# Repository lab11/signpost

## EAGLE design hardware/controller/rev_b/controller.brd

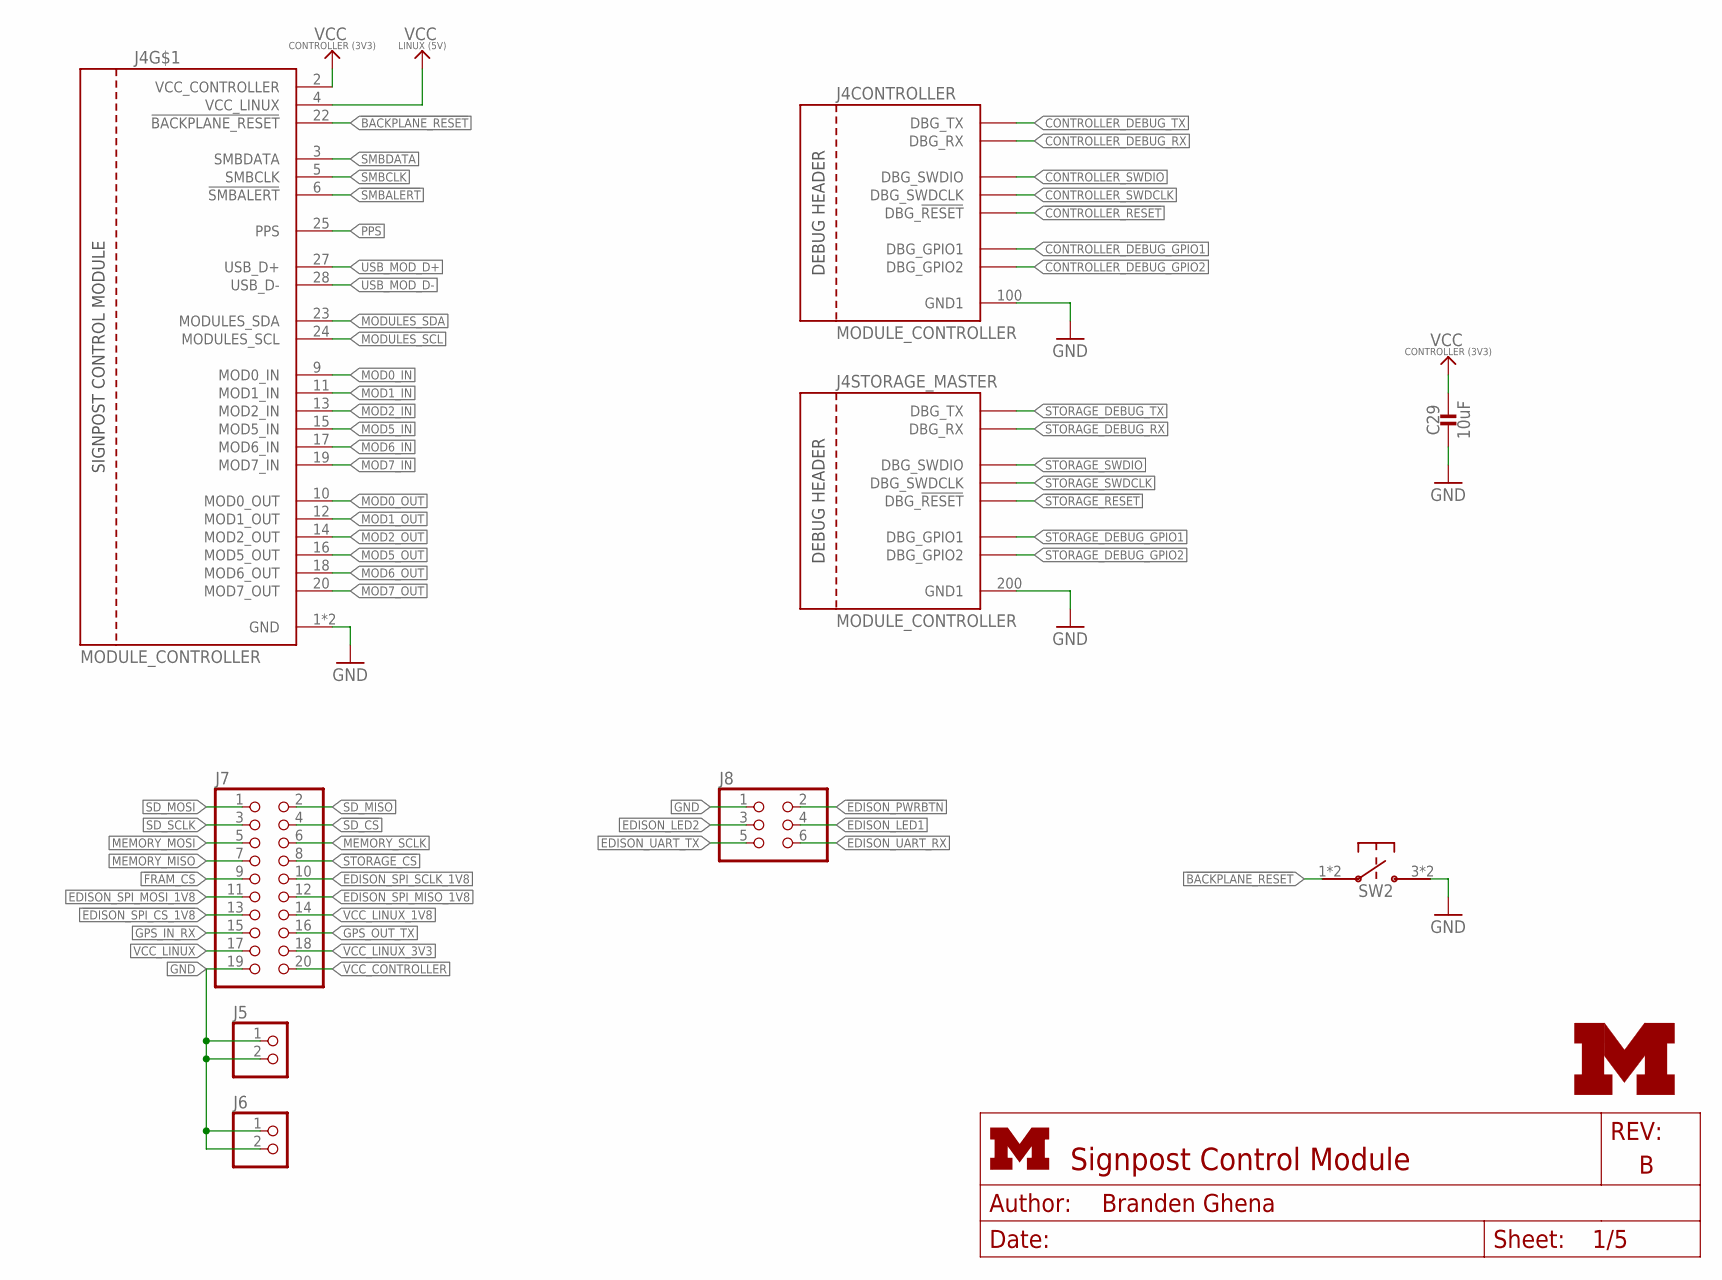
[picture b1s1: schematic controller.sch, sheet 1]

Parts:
C29: 10uF; 0402_CAP; DIGIKEY 490-13811-1-ND
J4: MODULE_CONTROLLER
J5, J6: PINHD-1X2; 1X02
J7: PINHD-2X10; 2X10
J8: PINHD-2X3; 2X03
LOGO1: UMICH_SOLID_MEDIUM; UMICH_SOLID_200MIL
SW2: PTS810SJ

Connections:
!BACKPLANE_RESET: J4.22 (!BACKPLANE_RESET), SW2.1, SW2.2
!CONTROLLER_RESET: J4.105 (DBG_!RESET); also elsewhere on the board
!EDISON_PWRBTN: J8.2; also elsewhere on the board
!EDISON_SPI_CS_1V8: J7.13; also elsewhere on the board
!FRAM_CS: J7.9; also elsewhere on the board
!SD_CS: J7.4; also elsewhere on the board
!SMBALERT: J4.6 (!SMBALERT); also elsewhere on the board
!STORAGE_CS: J7.8; also elsewhere on the board
!STORAGE_RESET: J4.205 (DBG_!RESET); also elsewhere on the board
CONTROLLER_DEBUG_GPIO1: J4.101 (DBG_GPIO1); also elsewhere on the board
CONTROLLER_DEBUG_GPIO2: J4.104 (DBG_GPIO2); also elsewhere on the board
CONTROLLER_DEBUG_RX: J4.103 (DBG_RX); also elsewhere on the board
CONTROLLER_DEBUG_TX: J4.102 (DBG_TX); also elsewhere on the board
CONTROLLER_SWDCLK: J4.106 (DBG_SWDCLK); also elsewhere on the board
CONTROLLER_SWDIO: J4.107 (DBG_SWDIO); also elsewhere on the board
EDISON_LED1: J8.4; also elsewhere on the board
EDISON_LED2: J8.3; also elsewhere on the board
EDISON_SPI_MISO_1V8: J7.12; also elsewhere on the board
EDISON_SPI_MOSI_1V8: J7.11; also elsewhere on the board
EDISON_SPI_SCLK_1V8: J7.10; also elsewhere on the board
EDISON_UART_RX: J8.6; also elsewhere on the board
EDISON_UART_TX: J8.5; also elsewhere on the board
GND: C29.2, J4.1 (GND), J4.21 (GND), J4.100 (GND1), J4.200 (GND1), J5.1, J5.2, J6.1, J6.2, J7.19, J8.1, SW2.3, SW2.4; also elsewhere on the board
GPS_IN_RX: J7.15; also elsewhere on the board
GPS_OUT_TX: J7.16; also elsewhere on the board
MEMORY_MISO: J7.7; also elsewhere on the board
MEMORY_MOSI: J7.5; also elsewhere on the board
MEMORY_SCLK: J7.6; also elsewhere on the board
MOD0_IN: J4.9 (MOD0_IN); also elsewhere on the board
MOD0_OUT: J4.10 (MOD0_OUT); also elsewhere on the board
MOD1_IN: J4.11 (MOD1_IN); also elsewhere on the board
MOD1_OUT: J4.12 (MOD1_OUT); also elsewhere on the board
MOD2_IN: J4.13 (MOD2_IN); also elsewhere on the board
MOD2_OUT: J4.14 (MOD2_OUT); also elsewhere on the board
MOD5_IN: J4.15 (MOD5_IN); also elsewhere on the board
MOD5_OUT: J4.16 (MOD5_OUT); also elsewhere on the board
MOD6_IN: J4.17 (MOD6_IN); also elsewhere on the board
MOD6_OUT: J4.18 (MOD6_OUT); also elsewhere on the board
MOD7_IN: J4.19 (MOD7_IN); also elsewhere on the board
MOD7_OUT: J4.20 (MOD7_OUT); also elsewhere on the board
MODULES_SCL: J4.24 (MODULES_SCL); also elsewhere on the board
MODULES_SDA: J4.23 (MODULES_SDA); also elsewhere on the board
PPS: J4.25 (PPS); also elsewhere on the board
SD_MISO: J7.2; also elsewhere on the board
SD_MOSI: J7.1; also elsewhere on the board
SD_SCLK: J7.3; also elsewhere on the board
SMBCLK: J4.5 (SMBCLK); also elsewhere on the board
SMBDATA: J4.3 (SMBDATA); also elsewhere on the board
STORAGE_DEBUG_GPIO1: J4.201 (DBG_GPIO1); also elsewhere on the board
STORAGE_DEBUG_GPIO2: J4.204 (DBG_GPIO2); also elsewhere on the board
STORAGE_DEBUG_RX: J4.203 (DBG_RX); also elsewhere on the board
STORAGE_DEBUG_TX: J4.202 (DBG_TX); also elsewhere on the board
STORAGE_SWDCLK: J4.206 (DBG_SWDCLK); also elsewhere on the board
STORAGE_SWDIO: J4.207 (DBG_SWDIO); also elsewhere on the board
USB_MOD_D+: J4.27 (USB_D+); also elsewhere on the board
USB_MOD_D-: J4.28 (USB_D-); also elsewhere on the board
VCC_CONTROLLER: C29.1, J4.2 (VCC_CONTROLLER), J7.20; also elsewhere on the board
VCC_LINUX: J4.4 (VCC_LINUX), J7.17; also elsewhere on the board
VCC_LINUX_1V8: J7.14; also elsewhere on the board
VCC_LINUX_3V3: J7.18; also elsewhere on the board

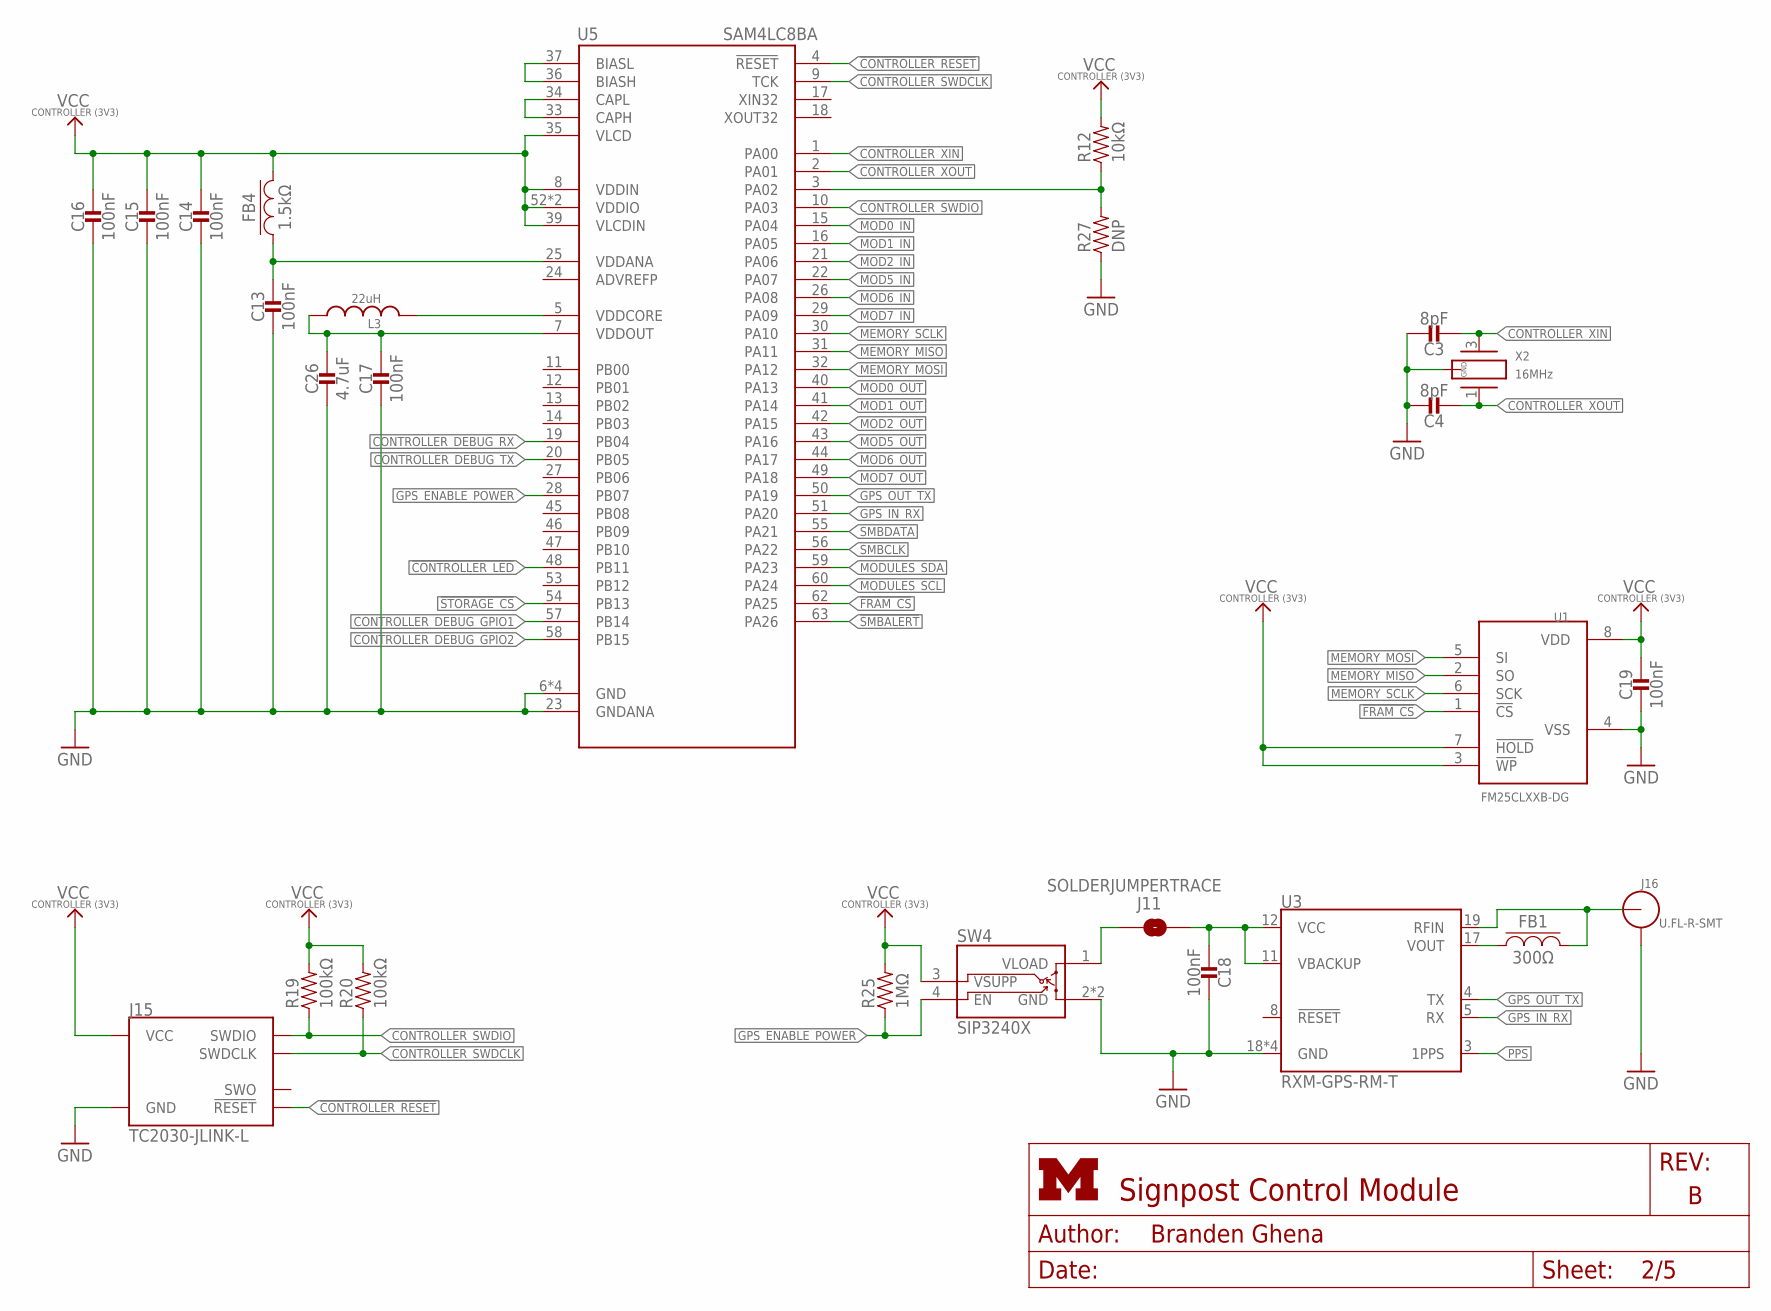
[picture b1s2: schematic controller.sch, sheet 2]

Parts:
C3, C4: 8pF; 0402_CAP; DIGIKEY 490-8230-1-ND
C13, C14, C15, C16, C17, C18, C19: 100nF; 0402_CAP; DIGIKEY 490-10777-1-ND
C26: 4.7uF; 0402_CAP; DIGIKEY 490-13252-1-ND
FB1: 300Ω; 0402_CAP; DIGIKEY ACML-0402-301-TCT-ND
FB4: 1.5kΩ; 0402_CAP; DIGIKEY 1276-6395-1-ND
J11: SOLDERJUMPERTRACE; SJ_2S-TRACE
J15: TC2030-JLINK-L; TC2030-IDC
J16: U.FL-R-SMT; U.FL_SMT
L3: 22uH; 1212
R12: 10kΩ; 0402_RES; DIGIKEY 1276-3431-1-ND
R19, R20: 100kΩ; 0402_RES; DIGIKEY 1276-3432-1-ND
R25: 1MΩ; 0402_RES; DIGIKEY 1276-3433-1-ND
R27: DNP; 0402_RES; DIGIKEY 1276-3431-1-ND
SW4: SIP3240X; TDFN4
U1: FM25CLXXB-DG; TDFN-8; DIGIKEY FM25CL64B-DGRA-ND
U3: RXM-GPS-RM-T
U5: SAM4LC8BA; QFN-64-9MM
X2: 16MHz; FHXXX

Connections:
!CONTROLLER_LED: U5.48 (PB11); also elsewhere on the board
!CONTROLLER_RESET: J15.3 (!RESET), U5.4 (!RESET); also elsewhere on the board
!FRAM_CS: U1.1 (!CS), U5.62 (PA25); also elsewhere on the board
!SMBALERT: U5.63 (PA26); also elsewhere on the board
!STORAGE_CS: U5.54 (PB13); also elsewhere on the board
CONTROLLER_BUCK/LDO_N: R12.1, R27.2, U5.3 (PA02)
CONTROLLER_DEBUG_GPIO1: U5.57 (PB14); also elsewhere on the board
CONTROLLER_DEBUG_GPIO2: U5.58 (PB15); also elsewhere on the board
CONTROLLER_DEBUG_RX: U5.19 (PB04); also elsewhere on the board
CONTROLLER_DEBUG_TX: U5.20 (PB05); also elsewhere on the board
CONTROLLER_SWDCLK: J15.4 (SWDCLK), R20.1, U5.9 (TCK); also elsewhere on the board
CONTROLLER_SWDIO: J15.2 (SWDIO), R19.1, U5.10 (PA03); also elsewhere on the board
CONTROLLER_XIN: C3.1, U5.1 (PA00), X2.3 (2)
CONTROLLER_XOUT: C4.1, U5.2 (PA01), X2.1
GND: C3.2, C4.2, C13.2, C14.2, C15.2, C16.2, C17.2, C18.2, C19.2, C26.2, J15.5 (GND), J16.GND1, J16.GND2, R27.1, SW4.2 (GND), SW4.PAD (GND), U1.4 (VSS), U3.18 (GND), U3.20 (GND), U3.21 (GND), U3.22 (GND), U5.6 (GND), U5.23 (GNDANA), U5.38 (GND), U5.64 (GND), U5.GND, X2.2 (GND), X2.4 (GND); also elsewhere on the board
GPS_ENABLE_POWER: R25.1, SW4.4 (EN), U5.28 (PB07)
GPS_IN_RX: U3.5 (RX), U5.51 (PA20); also elsewhere on the board
GPS_OUT_TX: U3.4 (TX), U5.50 (PA19); also elsewhere on the board
MEMORY_MISO: U1.2 (SO), U5.31 (PA11); also elsewhere on the board
MEMORY_MOSI: U1.5 (SI), U5.32 (PA12); also elsewhere on the board
MEMORY_SCLK: U1.6 (SCK), U5.30 (PA10); also elsewhere on the board
MOD0_IN: U5.15 (PA04); also elsewhere on the board
MOD0_OUT: U5.40 (PA13); also elsewhere on the board
MOD1_IN: U5.16 (PA05); also elsewhere on the board
MOD1_OUT: U5.41 (PA14); also elsewhere on the board
MOD2_IN: U5.21 (PA06); also elsewhere on the board
MOD2_OUT: U5.42 (PA15); also elsewhere on the board
MOD5_IN: U5.22 (PA07); also elsewhere on the board
MOD5_OUT: U5.43 (PA16); also elsewhere on the board
MOD6_IN: U5.26 (PA08); also elsewhere on the board
MOD6_OUT: U5.44 (PA17); also elsewhere on the board
MOD7_IN: U5.29 (PA09); also elsewhere on the board
MOD7_OUT: U5.49 (PA18); also elsewhere on the board
MODULES_SCL: U5.60 (PA24); also elsewhere on the board
MODULES_SDA: U5.59 (PA23); also elsewhere on the board
unnamed: FB1.1, U3.17 (VOUT)
unnamed: FB1.2, J16.SIG (ANT), U3.19 (RFIN)
unnamed: J11.1, SW4.1 (VLOAD)
unnamed: C13.1, FB4.1, U5.25 (VDDANA)
unnamed: C17.1, C26.1, L3.P$1 (1), U5.7 (VDDOUT)
unnamed: U5.36 (BIASH), U5.37 (BIASL)
unnamed: U5.33 (CAPH), U5.34 (CAPL)
unnamed: C18.1, J11.2, U3.11 (VBACKUP), U3.12 (VCC)
unnamed: L3.P$2 (2), U5.5 (VDDCORE)
PPS: U3.3 (1PPS); also elsewhere on the board
SMBCLK: U5.56 (PA22); also elsewhere on the board
SMBDATA: U5.55 (PA21); also elsewhere on the board
VCC_CONTROLLER: C14.1, C15.1, C16.1, C19.1, FB4.2, J15.1 (VCC), R12.2, R19.2, R20.2, R25.2, SW4.3 (VSUPP), U1.3 (!WP), U1.7 (!HOLD), U1.8 (VDD), U5.8 (VDDIN), U5.35 (VLCD), U5.39 (VLCDIN), U5.52 (VDDIO), U5.61 (VDDIO); also elsewhere on the board

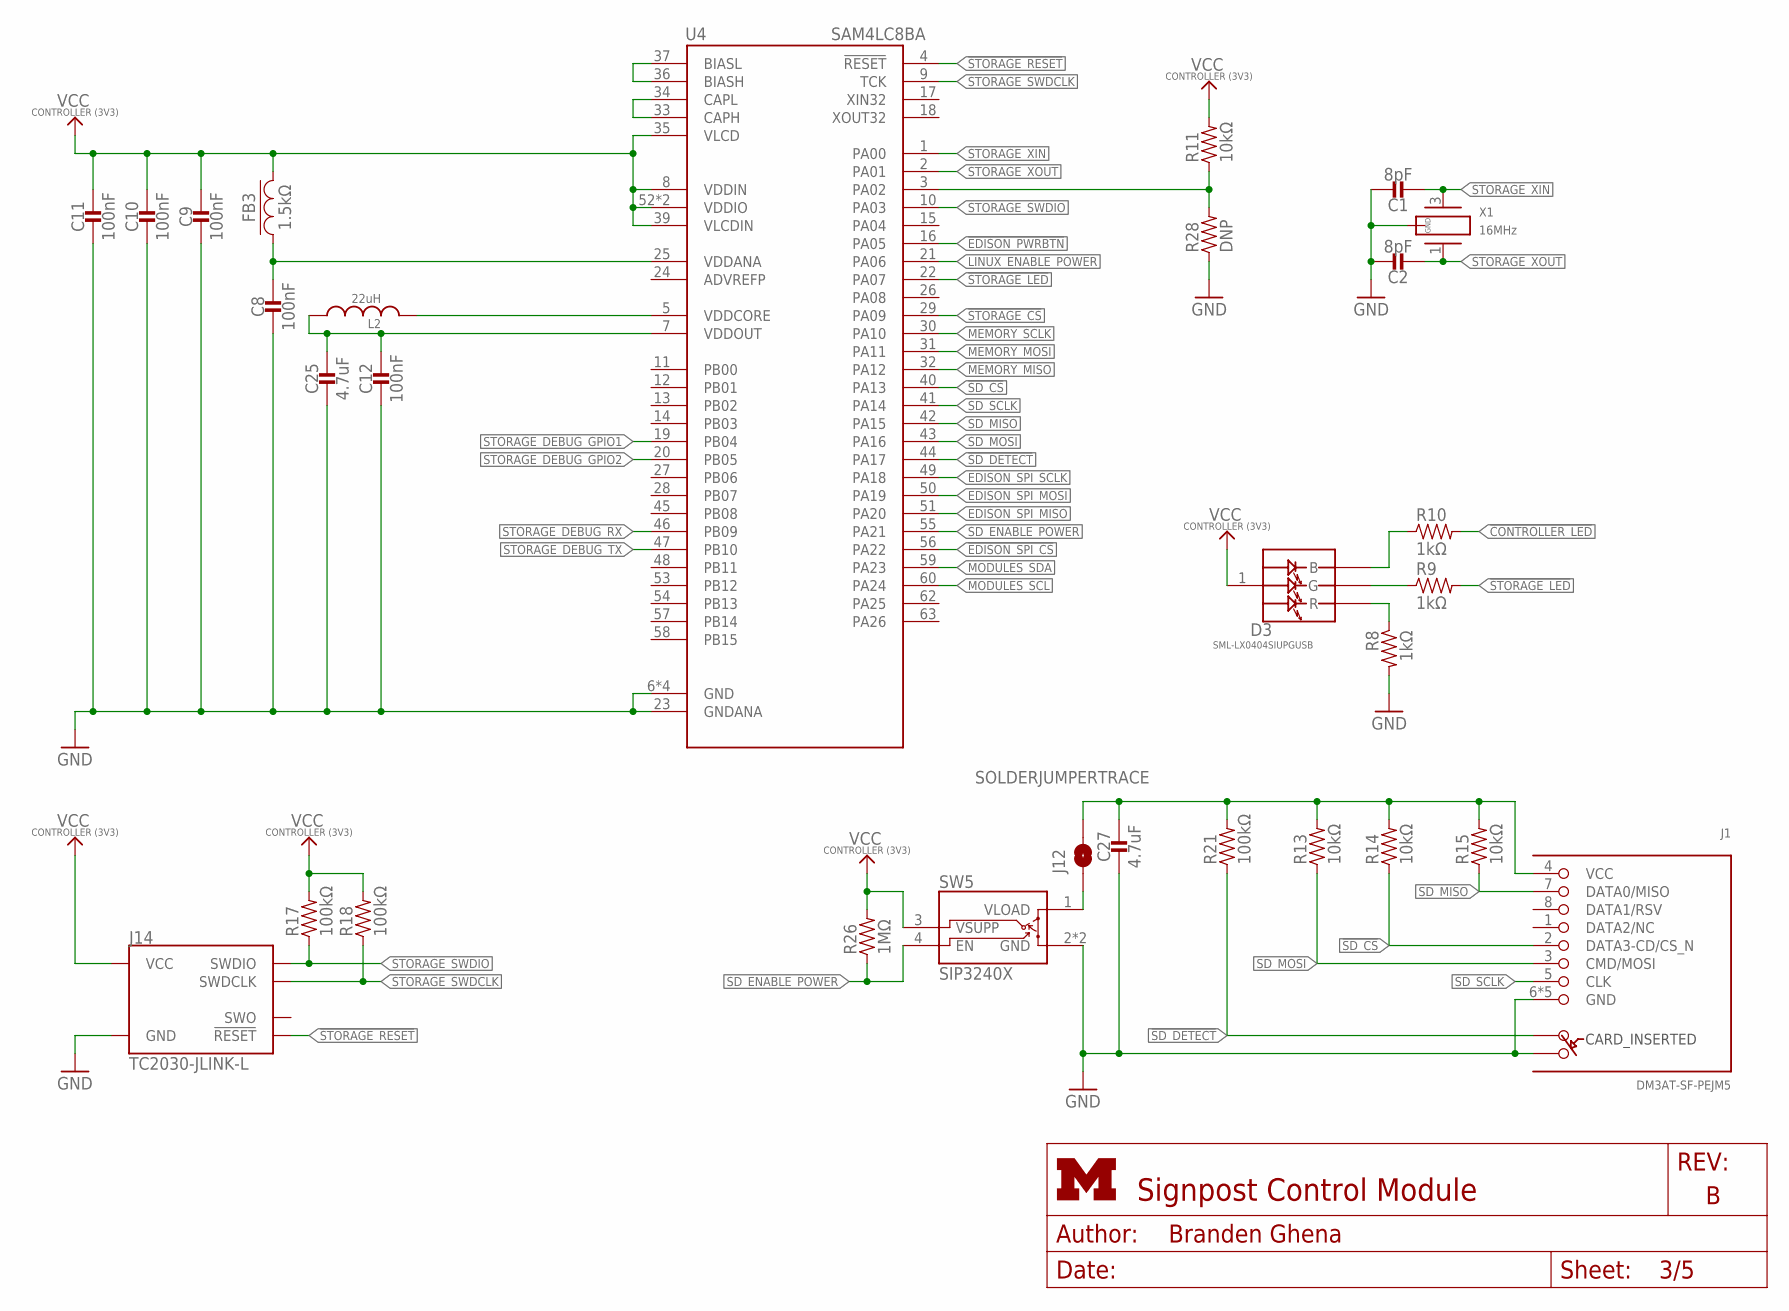
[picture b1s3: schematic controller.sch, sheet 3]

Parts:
C1, C2: 8pF; 0402_CAP; DIGIKEY 490-8230-1-ND
C8, C9, C10, C11, C12: 100nF; 0402_CAP; DIGIKEY 490-10777-1-ND
C25, C27: 4.7uF; 0402_CAP; DIGIKEY 490-13252-1-ND
D3: SML-LX0404SIUPGUSB; 1MM_SQ_4PAD
FB3: 1.5kΩ; 0402_CAP; DIGIKEY 1276-6395-1-ND
J1: DM3AT-SF-PEJM5
J12: SOLDERJUMPERTRACE; SJ_2S-TRACE
J14: TC2030-JLINK-L; TC2030-IDC
L2: 22uH; 1212
R8, R9, R10: 1kΩ; 0402_RES; DIGIKEY 1276-3430-1-ND
R11, R13, R14, R15: 10kΩ; 0402_RES; DIGIKEY 1276-3431-1-ND
R17, R18, R21: 100kΩ; 0402_RES; DIGIKEY 1276-3432-1-ND
R26: 1MΩ; 0402_RES; DIGIKEY 1276-3433-1-ND
R28: DNP; 0402_RES; DIGIKEY 1276-3431-1-ND
SW5: SIP3240X; TDFN4
U4: SAM4LC8BA; QFN-64-9MM
X1: 16MHz; FHXXX

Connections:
!CONTROLLER_LED: R10.2; also elsewhere on the board
!EDISON_PWRBTN: U4.16 (PA05); also elsewhere on the board
!EDISON_SPI_CS: U4.56 (PA22); also elsewhere on the board
!SD_CS: J1.2 (DATA3-CD/CS_N), R14.1, U4.40 (PA13); also elsewhere on the board
!SD_DETECT: J1.A, R21.1, U4.44 (PA17)
!STORAGE_CS: U4.29 (PA09); also elsewhere on the board
!STORAGE_LED: R9.2, U4.22 (PA07)
!STORAGE_RESET: J14.3 (!RESET), U4.4 (!RESET); also elsewhere on the board
EDISON_SPI_MISO: U4.51 (PA20); also elsewhere on the board
EDISON_SPI_MOSI: U4.50 (PA19); also elsewhere on the board
EDISON_SPI_SCLK: U4.49 (PA18); also elsewhere on the board
GND: C1.2, C2.2, C8.2, C9.2, C10.2, C11.2, C12.2, C25.2, C27.2, J1.6 (GND), J1.B, J1.MOUNT0 (GND), J1.MOUNT1 (GND), J1.MOUNT2 (GND), J1.MOUNT3 (GND), J14.5 (GND), R8.2, R28.1, SW5.2 (GND), SW5.PAD (GND), U4.6 (GND), U4.23 (GNDANA), U4.38 (GND), U4.64 (GND), U4.GND, X1.2 (GND), X1.4 (GND); also elsewhere on the board
LINUX_ENABLE_POWER: U4.21 (PA06); also elsewhere on the board
MEMORY_MISO: U4.32 (PA12); also elsewhere on the board
MEMORY_MOSI: U4.31 (PA11); also elsewhere on the board
MEMORY_SCLK: U4.30 (PA10); also elsewhere on the board
MODULES_SCL: U4.60 (PA24); also elsewhere on the board
MODULES_SDA: U4.59 (PA23); also elsewhere on the board
unnamed: D3.2 (R), R8.1
unnamed: D3.4 (G), R9.1
unnamed: D3.3 (B), R10.1
unnamed: J12.1, SW5.1 (VLOAD)
unnamed: C8.1, FB3.1, U4.25 (VDDANA)
unnamed: C12.1, C25.1, L2.P$1 (1), U4.7 (VDDOUT)
unnamed: L2.P$2 (2), U4.5 (VDDCORE)
unnamed: U4.33 (CAPH), U4.34 (CAPL)
unnamed: U4.36 (BIASH), U4.37 (BIASL)
unnamed: C27.1, J1.4 (VCC), J12.2, R13.2, R14.2, R15.2, R21.2
SD_ENABLE_POWER: R26.1, SW5.4 (EN), U4.55 (PA21)
SD_MISO: J1.7 (DATA0/MISO), R15.1, U4.42 (PA15); also elsewhere on the board
SD_MOSI: J1.3 (CMD/MOSI), R13.1, U4.43 (PA16); also elsewhere on the board
SD_SCLK: J1.5 (CLK), U4.41 (PA14); also elsewhere on the board
STORAGE_BUCK/LDO_N: R11.1, R28.2, U4.3 (PA02)
STORAGE_DEBUG_GPIO1: U4.19 (PB04); also elsewhere on the board
STORAGE_DEBUG_GPIO2: U4.20 (PB05); also elsewhere on the board
STORAGE_DEBUG_RX: U4.46 (PB09); also elsewhere on the board
STORAGE_DEBUG_TX: U4.47 (PB10); also elsewhere on the board
STORAGE_SWDCLK: J14.4 (SWDCLK), R18.1, U4.9 (TCK); also elsewhere on the board
STORAGE_SWDIO: J14.2 (SWDIO), R17.1, U4.10 (PA03); also elsewhere on the board
STORAGE_XIN: C1.1, U4.1 (PA00), X1.3 (2)
STORAGE_XOUT: C2.1, U4.2 (PA01), X1.1
VCC_CONTROLLER: C9.1, C10.1, C11.1, D3.1 (VDD), FB3.2, J14.1 (VCC), R11.2, R17.2, R18.2, R26.2, SW5.3 (VSUPP), U4.8 (VDDIN), U4.35 (VLCD), U4.39 (VLCDIN), U4.52 (VDDIO), U4.61 (VDDIO); also elsewhere on the board

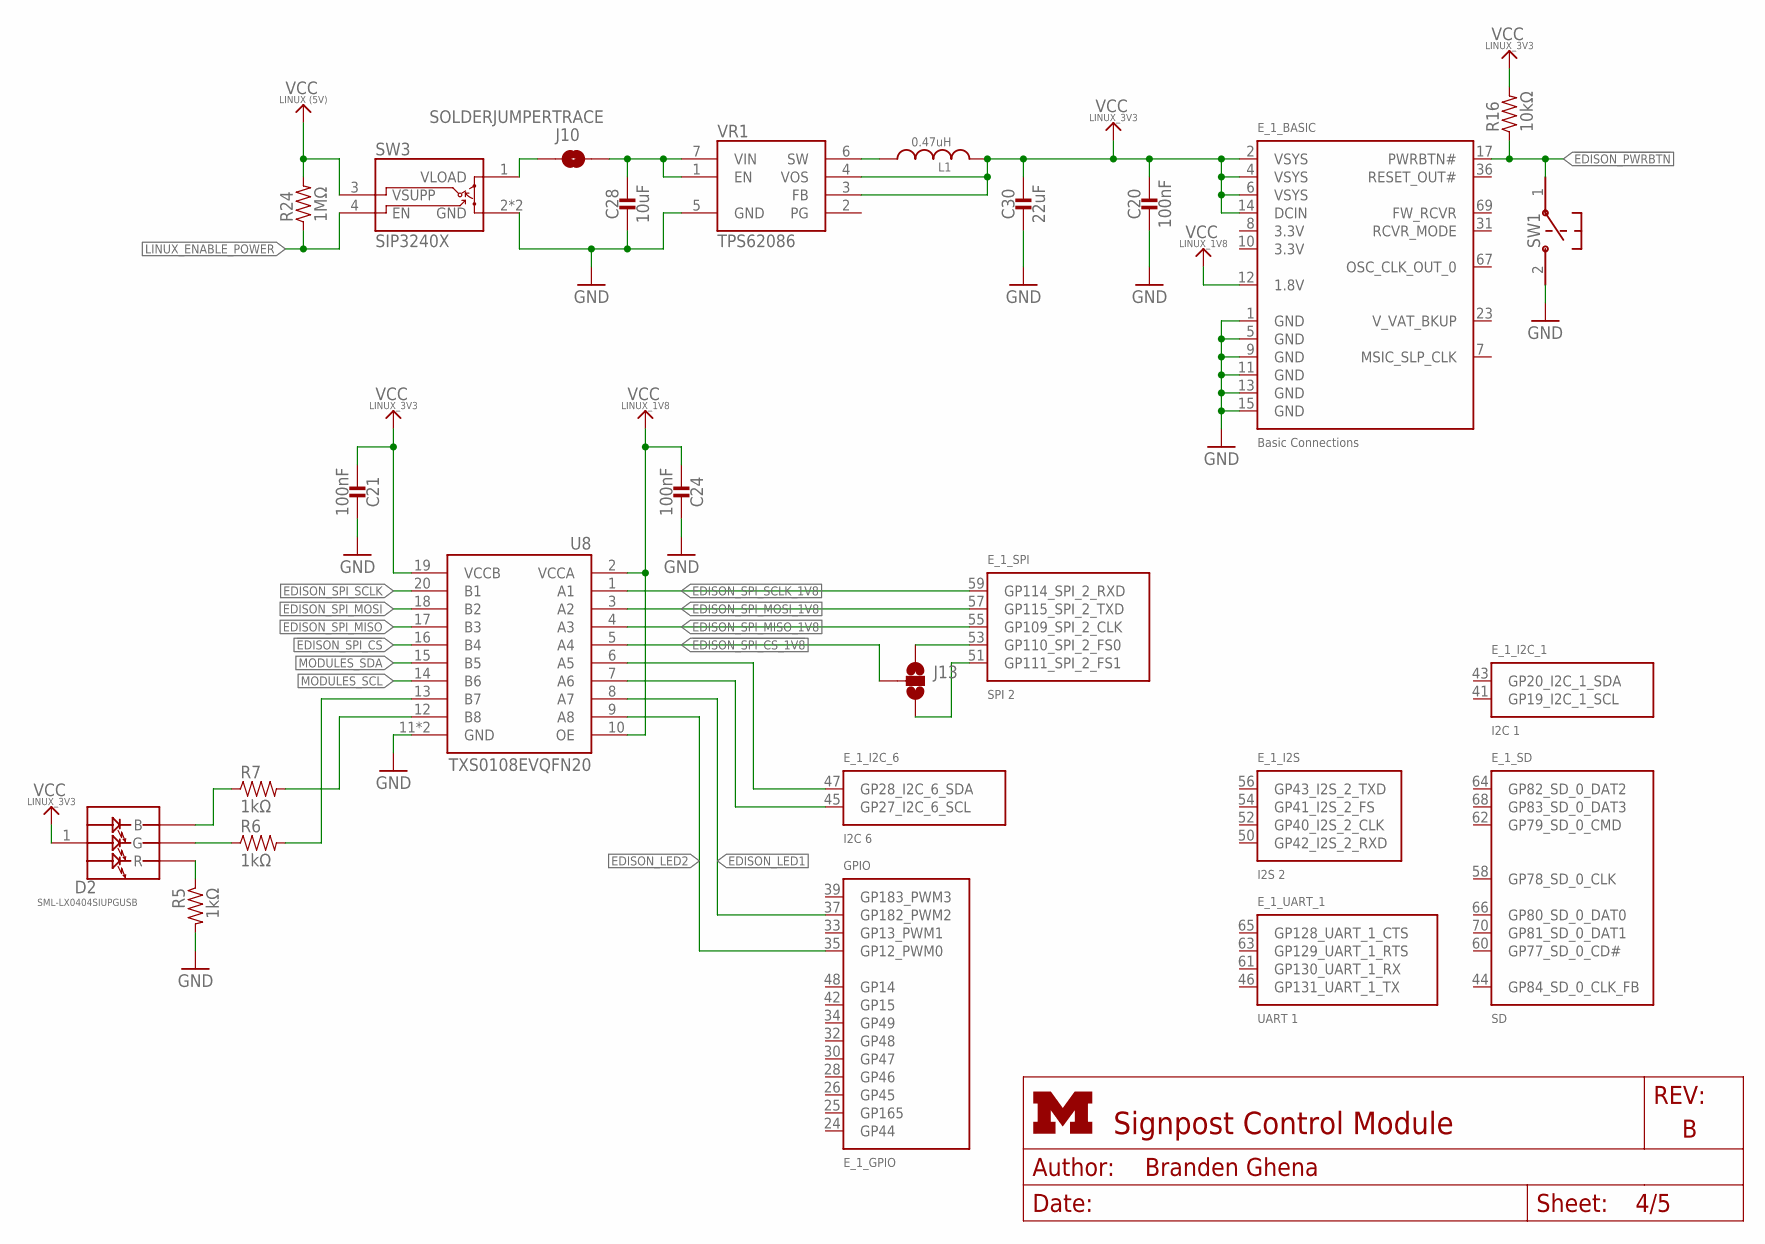
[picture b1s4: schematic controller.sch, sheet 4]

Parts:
C20, C21, C24: 100nF; 0402_CAP; DIGIKEY 490-10777-1-ND
C28: 10uF; 0805_CAP; DIGIKEY 490-8316-1-ND
C30: 22uF; 0805_CAP; DIGIKEY 490-1719-1-ND
D2: SML-LX0404SIUPGUSB; 1MM_SQ_4PAD
E_1: EDISON_CONNECTOR_SEGMENTED; EDISON_DAUGHTER; MOUSER 798-DF40HC3070DS4V51
J10: SOLDERJUMPERTRACE; SJ_2S-TRACE
J13: SOLDERJUMPER_2WAYPASTE2&3; SJ_3_PASTE2&3
L1: 0.47uH; DFE322512C; DIGIKEY 490-10596-1-ND
R5, R6, R7: 1kΩ; 0402_RES; DIGIKEY 1276-3430-1-ND
R16: 10kΩ; 0402_RES; DIGIKEY 1276-3431-1-ND
R24: 1MΩ; 0402_RES; DIGIKEY 1276-3433-1-ND
SW1: B3U-1000P
SW3: SIP3240X; TDFN4
U8: TXS0108EVQFN20; R-PVQFN-N20; DIGIKEY 296-24806-1-ND
VR1: TPS62086; RLT0007A

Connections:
!EDISON_PWRBTN: E_1.17 (PWRBTN#), R16.1, SW1.1; also elsewhere on the board
!EDISON_SPI_CS: U8.16 (B4); also elsewhere on the board
!EDISON_SPI_CS_1V8: J13.2, U8.5 (A4); also elsewhere on the board
EDISON_LED1: E_1.37 (GP182_PWM2), U8.8 (A7); also elsewhere on the board
EDISON_LED2: E_1.35 (GP12_PWM0), U8.9 (A8); also elsewhere on the board
EDISON_SPI_MISO: U8.17 (B3); also elsewhere on the board
EDISON_SPI_MISO_1V8: E_1.55 (GP109_SPI_2_CLK), U8.4 (A3); also elsewhere on the board
EDISON_SPI_MOSI: U8.18 (B2); also elsewhere on the board
EDISON_SPI_MOSI_1V8: E_1.57 (GP115_SPI_2_TXD), U8.3 (A2); also elsewhere on the board
EDISON_SPI_SCLK: U8.20 (B1); also elsewhere on the board
EDISON_SPI_SCLK_1V8: E_1.59 (GP114_SPI_2_RXD), U8.1 (A1); also elsewhere on the board
GND: C20.2, C21.1, C24.1, C28.P$2 (2), C30.P$2 (2), E_1.1 (GND), E_1.5 (GND), E_1.9 (GND), E_1.11 (GND), E_1.13 (GND), E_1.15 (GND), R5.2, SW1.2, SW3.2 (GND), SW3.PAD (GND), U8.11 (GND), U8.THERMAL (GND), VR1.5 (GND); also elsewhere on the board
LINUX_5V_IN: C28.P$1 (1), J10.2, VR1.1 (EN), VR1.7 (VIN)
LINUX_ENABLE_POWER: R24.1, SW3.4 (EN); also elsewhere on the board
MODULES_SCL: U8.14 (B6); also elsewhere on the board
MODULES_SCL_1V8: E_1.45 (GP27_I2C_6_SCL), U8.7 (A6)
MODULES_SDA: U8.15 (B5); also elsewhere on the board
MODULES_SDA_1V8: E_1.47 (GP28_I2C_6_SDA), U8.6 (A5)
unnamed: E_1.53 (GP110_SPI_2_FS0), J13.1
unnamed: R7.2, U8.12 (B8)
unnamed: E_1.51 (GP111_SPI_2_FS1), J13.3
unnamed: L1.P$1 (1), VR1.6 (SW)
unnamed: J10.1, SW3.1 (VLOAD)
unnamed: D2.2 (R), R5.1
unnamed: D2.4 (G), R6.1
unnamed: D2.3 (B), R7.1
unnamed: R6.2, U8.13 (B7)
VCC_LINUX: R24.2, SW3.3 (VSUPP); also elsewhere on the board
VCC_LINUX_1V8: C24.2, E_1.12 (1.8V), U8.2 (VCCA), U8.10 (OE); also elsewhere on the board
VCC_LINUX_3V3: C20.1, C21.2, C30.P$1 (1), D2.1 (VDD), E_1.2 (VSYS), E_1.4 (VSYS), E_1.6 (VSYS), E_1.14 (DCIN), L1.P$2 (2), R16.2, U8.19 (VCCB), VR1.3 (FB), VR1.4 (VOS); also elsewhere on the board

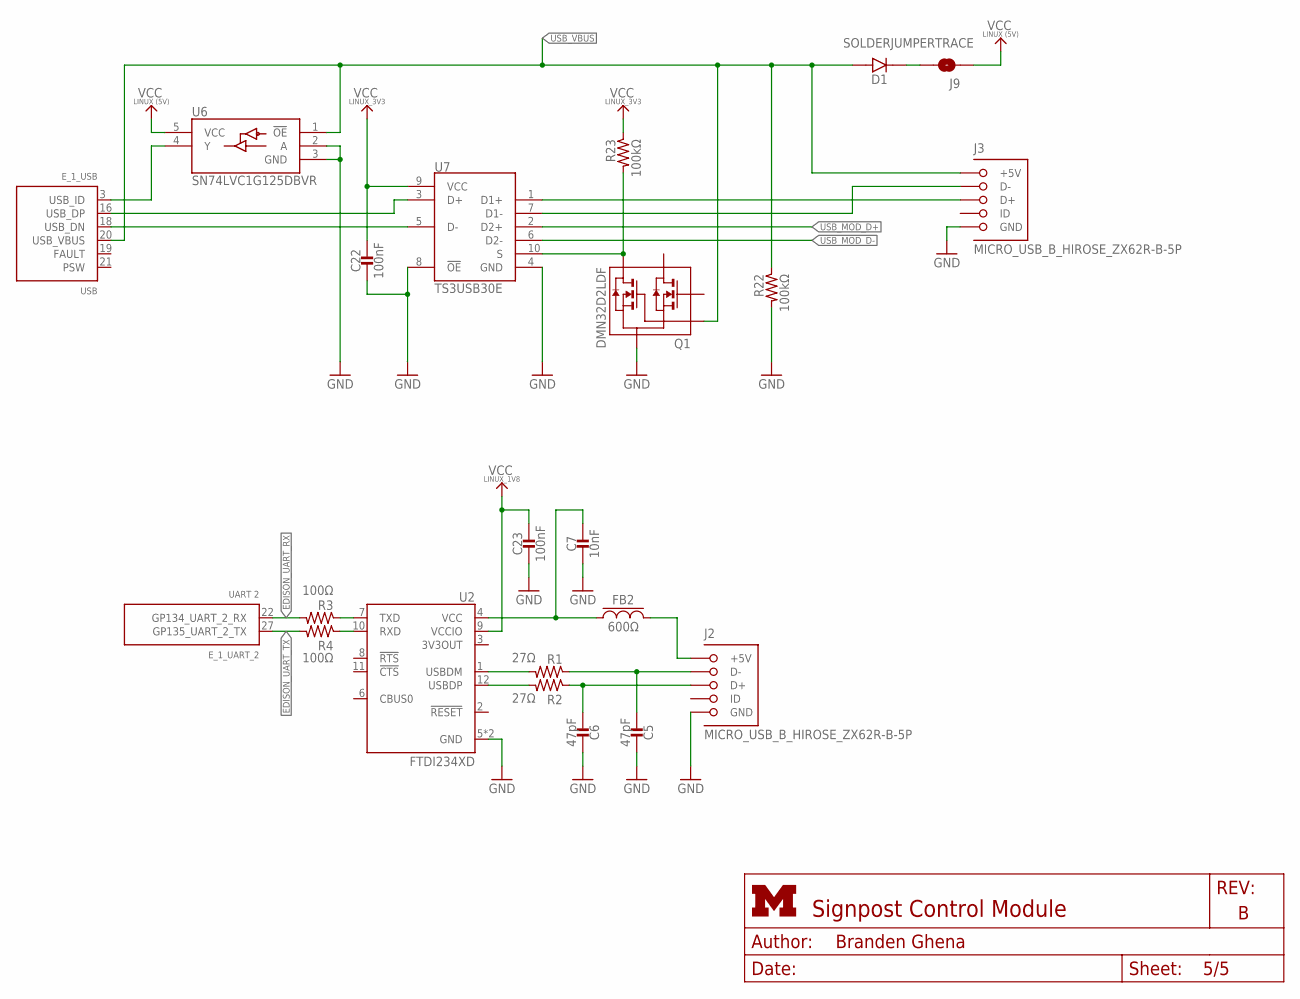
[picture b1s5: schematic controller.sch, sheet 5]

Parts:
C5, C6: 47pF; 0402_CAP; DIGIKEY 490-6241-1-ND
C7: 10nF; 0402_CAP; DIGIKEY 490-6296-1-ND
C22, C23: 100nF; 0402_CAP; DIGIKEY 490-10777-1-ND
D1: DIODE; 0805_DIODE; DIGIKEY 478-7800-1-ND
E_1: EDISON_CONNECTOR_SEGMENTED; EDISON_DAUGHTER; MOUSER 798-DF40HC3070DS4V51
FB2: 600Ω; 0805_CAP; DIGIKEY 240-2390-1-ND
J2, J3: MICRO_USB_B_HIROSE_ZX62R-B-5P; USB_MICRO_B-HIROSE-ZX62R-B-5P; DIGIKEY H125274CT-ND
J9: SOLDERJUMPERTRACE; SJ_2S-TRACE
Q1: DMN32D2LDF; SOT353
R1, R2: 27Ω; 0402_RES; DIGIKEY 1276-3907-1-ND
R3, R4: 100Ω; 0402_RES; DIGIKEY 1276-3429-1-ND
R22, R23: 100kΩ; 0402_RES; DIGIKEY 1276-3432-1-ND
U2: FTDI234XD; DFN-12/3MM
U6: SN74LVC1G125DBVR; SOT-23-5
U7: TS3USB30E; UQFN-10

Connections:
D+: C6.1, J2.3 (D+), R2.1
D-: C5.1, J2.2 (D-), R1.1
EDISON_UART_RX: E_1.22 (GP134_UART_2_RX), R3.2; also elsewhere on the board
EDISON_UART_TX: E_1.27 (GP135_UART_2_TX), R4.2; also elsewhere on the board
GND: C5.2, C6.2, C7.2, C22.2, C23.2, J2.5 (GND), J3.5 (GND), Q1.S, R22.2, U2.5 (GND), U2.13 (GND), U6.2 (A), U6.3 (GND), U7.4 (GND), U7.8 (!OE); also elsewhere on the board
unnamed: R1.2, U2.1 (USBDM)
unnamed: R2.2, U2.12 (USBDP)
unnamed: J3.2 (D-), U7.7 (D1-)
unnamed: J3.3 (D+), U7.1 (D1+)
unnamed: FB2.P$2, J2.1 (+5V)
unnamed: D1.CATHODE, J9.2
unnamed: E_1.3 (USB_ID), U6.4 (Y)
unnamed: R3.1, U2.7 (TXD)
unnamed: R4.1, U2.10 (RXD)
unnamed: C7.1, FB2.P$1, U2.4 (VCC)
unnamed: Q1.D2, R23.2, U7.10 (S)
USB_D+: E_1.16 (USB_DP), U7.3 (D+)
USB_D-: E_1.18 (USB_DN), U7.5 (D-)
USB_MOD_D+: U7.2 (D2+); also elsewhere on the board
USB_MOD_D-: U7.6 (D2-); also elsewhere on the board
USB_VBUS: D1.ANODE, E_1.20 (USB_VBUS), J3.1 (+5V), Q1.G2, R22.1, U6.1 (!OE)
VCC_LINUX: J9.1, U6.5 (VCC); also elsewhere on the board
VCC_LINUX_1V8: C23.1, U2.9 (VCCIO); also elsewhere on the board
VCC_LINUX_3V3: C22.1, R23.1, U7.9 (VCC); also elsewhere on the board

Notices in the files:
parts and their libraries:
SparkFun-Passives: Licensing: CC v3.0 Share-Alike You are welcome to use this library for commercial purposes.
